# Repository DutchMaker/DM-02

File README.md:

# DM-02 8-Bit Computer

_Pronounced: "Dee-Em Zero Two"_

**An 8-bit computer built (almost) entirely out of TTL logic chips**  
This project started in September 2019 and is currently in progress.  
Please refer to the [documentation](./Documentation) for the project status.

**[Start by reading the introduction](./Documentation/)**

If you would like to see the computer in action, the best I can offer you now is the [DM-02 Emulator](https://dutchmaker.com/dm-02/emulator) while the electronic version is under development.

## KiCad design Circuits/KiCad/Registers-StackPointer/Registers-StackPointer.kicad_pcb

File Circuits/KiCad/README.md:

# KiCad projects

KiCad EDA is used for all circuit diagrams and PCB design.
Get it for free at: [http://kicad-pcb.org](http://kicad-pcb.org)

### KiCad setup:

- Add `./Libraries/*.lib` as global Symbol library to KiCad (Eeschema)
- Add the `./Libraries` folder as global Footprint library to KiCad (Pcbnew)

### Notes:

- The _FreeRouting_ application (`./Libraries/freeRouting.jar`) is used for initial PCB routing

### Credits:

- Arduino Mega Shield component: https://github.com/Alarm-Siren/arduino-kicad-library
- FreeRouting: https://freerouting.org/

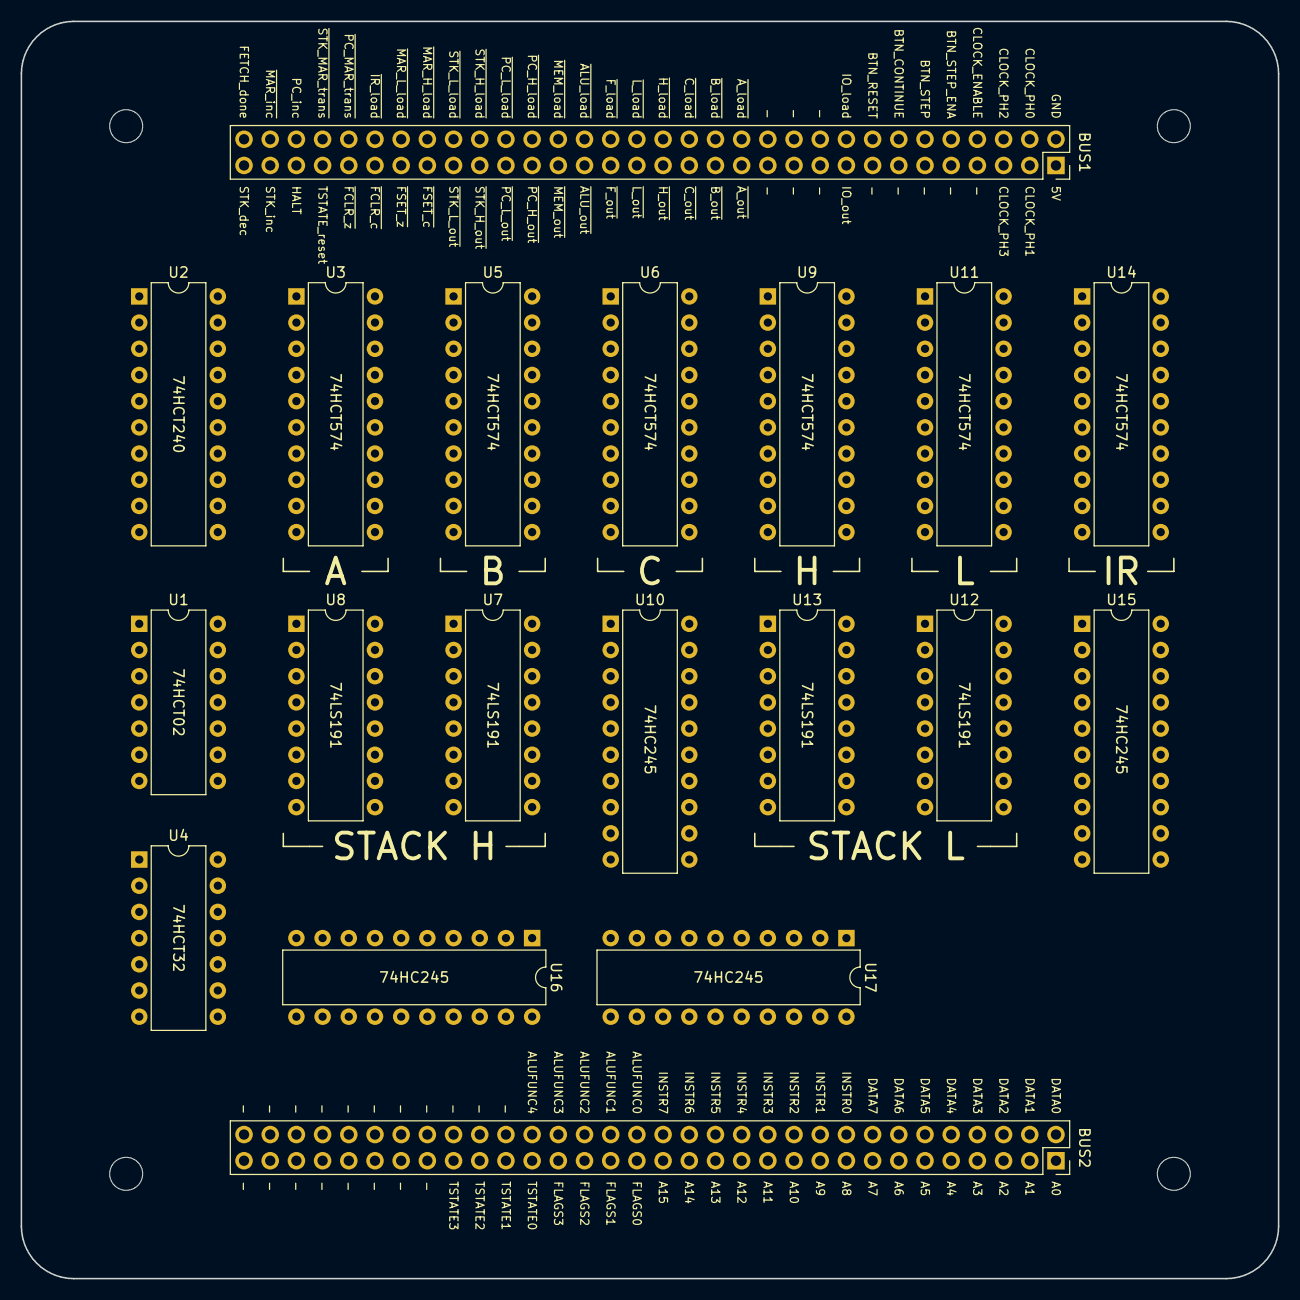
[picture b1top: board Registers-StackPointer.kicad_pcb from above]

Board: 2 copper layers, 121.9 x 121.9 mm, 23 parts (0 on the bottom side), 84 nets, no tracks yet.

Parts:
BUS1, BUS2: Conn_02x32_Odd_Even; PinSocket_2x32_P2.54mm_Vertical
H1, H2, H3, H4: MountingHole; MountingHole_3.2mm_M3
U1: 74HCT02; DIP-14_W7.62mm
U2: 74HCT240; DIP-20_W7.62mm
U3, U5, U6, U9, U11, U14: 74HCT574; DIP-20_W7.62mm
U4: 74HCT32; DIP-14_W7.62mm
U7, U8, U12, U13: 74LS191; DIP-16_W7.62mm
U10, U15, U16, U17: 74HC245; DIP-20_W7.62mm

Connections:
5V: BUS1.1, U2.20, U3.20, U5.20, U6.20, U7.16, U8.16, U9.20, U10.20, U11.20, U12.16, U13.16, U14.20, U15.20, U16.20, U17.20
A0: BUS2.1, U17.18
A1: BUS2.3, U17.17
A2: BUS2.5, U17.16
A3: BUS2.7, U17.15
A4: BUS2.9, U17.14
A5: BUS2.11, U17.13
A6: BUS2.13, U17.12
A7: BUS2.15, U17.11
A8: BUS2.17, U16.18
A9: BUS2.19, U16.17
A10: BUS2.21, U16.16
A11: BUS2.23, U16.15
A12: BUS2.25, U16.14
A13: BUS2.27, U16.13
A14: BUS2.29, U16.12
A15: BUS2.31, U16.11
A_clock: U2.18, U3.11
B_clock: U2.16, U5.11
CLOCK_PH3: BUS1.5, U1.11, U1.12, U4.2, U4.4, U12.14
C_clock: U2.14, U6.11
D0: U3.2, U3.19, U5.2, U5.19, U6.2, U6.19, U7.15, U9.2, U9.19, U10.18, U11.2, U11.19, U12.15, U14.2, U15.18
D1: U3.3, U3.18, U5.3, U5.18, U6.3, U6.18, U7.1, U9.3, U9.18, U10.17, U11.3, U11.18, U12.1, U14.3, U15.17
D2: U3.4, U3.17, U5.4, U5.17, U6.4, U6.17, U7.10, U9.4, U9.17, U10.16, U11.4, U11.17, U12.10, U14.4, U15.16
D3: U3.5, U3.16, U5.5, U5.16, U6.5, U6.16, U7.9, U9.5, U9.16, U10.15, U11.5, U11.16, U12.9, U14.5, U15.15
D4: U3.6, U3.15, U5.6, U5.15, U6.6, U6.15, U8.15, U9.6, U9.15, U10.14, U11.6, U11.15, U13.15, U14.6, U15.14
D5: U3.7, U3.14, U5.7, U5.14, U6.7, U6.14, U8.1, U9.7, U9.14, U10.13, U11.7, U11.14, U13.1, U14.7, U15.13
D6: U3.8, U3.13, U5.8, U5.13, U6.8, U6.13, U8.10, U9.8, U9.13, U10.12, U11.8, U11.13, U13.10, U14.8, U15.12
D7: U3.9, U3.12, U5.9, U5.12, U6.9, U6.12, U8.9, U9.9, U9.12, U10.11, U11.9, U11.12, U13.9, U14.9, U15.11
DOWN_~UP: U1.1, U1.5, U7.5, U8.5, U12.5, U13.5
GND: BUS1.2, U2.10, U3.10, U5.10, U6.10, U7.8, U8.8, U9.10, U10.1, U10.10, U11.10, U12.8, U13.8, U14.1, U14.10, U15.1, U15.10, U16.1, U16.10, U17.1, U17.10
HIGH0_Rc: U7.13, U8.14
H_clock: U2.12, U9.11
INSTR0: BUS2.18, U14.19
INSTR1: BUS2.20, U14.18
INSTR2: BUS2.22, U14.17
INSTR3: BUS2.24, U14.16
INSTR4: BUS2.26, U14.15
INSTR5: BUS2.28, U14.14
INSTR6: BUS2.30, U14.13
INSTR7: BUS2.32, U14.12
IR_clock: U2.5, U14.11
LOW0_Rc: U12.13, U13.14
LOW1_Rc: U7.14, U13.13
L_clock: U2.3, U11.11
unnamed: U1.3, U1.4
unnamed: U1.13, U2.1, U2.19
unnamed: U7.3, U10.2, U16.2
unnamed: U7.2, U10.3, U16.3
unnamed: U7.6, U10.4, U16.4
unnamed: U7.7, U10.5, U16.5
unnamed: U8.3, U10.6, U16.6
unnamed: U8.2, U10.7, U16.7
unnamed: U8.6, U10.8, U16.8
unnamed: U8.7, U10.9, U16.9
unnamed: U12.2, U15.3, U17.3
unnamed: U12.3, U15.2, U17.2
unnamed: U12.6, U15.4, U17.4
unnamed: U12.7, U15.5, U17.5
unnamed: U13.2, U15.7, U17.7
unnamed: U13.3, U15.6, U17.6
unnamed: U13.6, U15.8, U17.8
unnamed: U13.7, U15.9, U17.9
STK_dec: BUS1.63, U1.6, U1.9
STK_inc: BUS1.61, U1.2, U1.8
~A_load: BUS1.26, U2.2
~A_out: BUS1.25, U3.1
~B_load: BUS1.28, U2.4
~B_out: BUS1.27, U5.1
~CLK_EN: U1.10, U7.4, U8.4, U12.4, U13.4
~C_load: BUS1.30, U2.6
~C_out: BUS1.29, U6.1
~HIGH_PL: U4.3, U7.11, U8.11
~H_load: BUS1.32, U2.8
~H_out: BUS1.31, U9.1
~IR_load: BUS1.54, U2.15
~LOW_PL: U4.6, U12.11, U13.11
~L_load: BUS1.34, U2.17
~L_out: BUS1.33, U11.1
~STK_H_load: BUS1.46, U4.1
~STK_H_out: BUS1.45, U10.19
~STK_L_load: BUS1.48, U4.5
~STK_L_out: BUS1.47, U15.19
~STK_MAR_transfer: BUS1.58, U16.19, U17.19

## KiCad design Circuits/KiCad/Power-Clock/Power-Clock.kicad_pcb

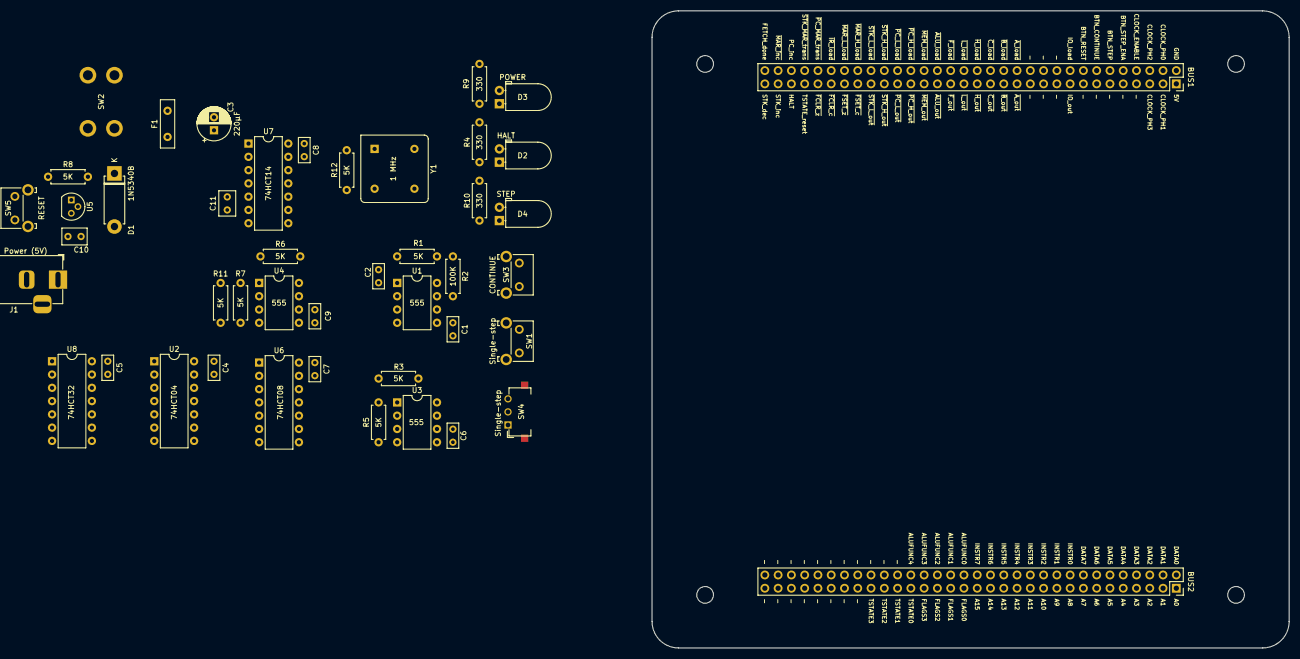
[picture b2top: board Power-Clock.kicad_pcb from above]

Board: 2 copper layers, 121.9 x 121.9 mm, 49 parts (0 on the bottom side), 34 nets, no tracks yet.

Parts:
BUS1, BUS2: Conn_02x32_Odd_Even; PinSocket_2x32_P2.54mm_Vertical
C1, C6, C9: 10nF; C_Rect_L4.6mm_W2.0mm_P2.50mm_MKS02_FKP02
C2, C4, C5, C7, C8: 100nF; C_Rect_L4.6mm_W2.0mm_P2.50mm_MKS02_FKP02
C3: 220µF; CP_Radial_D6.3mm_P2.50mm
C10: 100 nF; C_Rect_L4.6mm_W3.0mm_P2.50mm_MKS02_FKP02
C11: 1nF; C_Rect_L4.6mm_W3.0mm_P2.50mm_MKS02_FKP02
D1: 1N5340B; D_5W_P10.16mm_Horizontal
D2: HALT; LED_D5.0mm_Horizontal_O1.27mm_Z3.0mm
D3: POWER; LED_D5.0mm_Horizontal_O1.27mm_Z3.0mm
D4: STEP; LED_D5.0mm_Horizontal_O1.27mm_Z3.0mm
F1: Polyfuse; C_Disc_D9.0mm_W2.5mm_P5.00mm
H1, H2, H3, H4: MountingHole; MountingHole_3.2mm_M3
J1: Power (5V); BarrelJack_Horizontal
R1, R3, R5, R6, R7, R8, R11, R12: 5K; R_Axial_DIN0207_L6.3mm_D2.5mm_P7.62mm_Horizontal
R2: 100K; R_Axial_DIN0207_L6.3mm_D2.5mm_P7.62mm_Horizontal
R4, R9, R10: 330; R_Axial_DIN0207_L6.3mm_D2.5mm_P7.62mm_Horizontal
SW1: Single-step; SW_Tactile_SKHH_Angled
SW2: Power; Switch_DPST_Angled
SW3: CONTINUE; SW_Tactile_SKHH_Angled
SW4: Single-step; Slide-switch
SW5: RESET; SW_Tactile_SKHH_Angled
U1, U3, U4: 555; DIP-8_W7.62mm
U2: 74HCT04; DIP-14_W7.62mm
U5: MCP100-450D; TO-92
U6: 74HCT08; DIP-14_W7.62mm
U7: 74HCT14; DIP-14_W7.62mm
U8: 74HCT32; DIP-14_W7.62mm
Y1: 1 MHz; Oscillator_DIP-8_v2

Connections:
CLK_OSC: U6.5, Y1.3
CLK_STEP: U1.3, U6.1
CLOCK1: U6.11, U7.1, U7.3
CLOCK2: U7.6, U7.9
CLOCK_ENABLE: R12.2, U6.12
COMPUTER_5V: C3.1, C4.1, C5.1, C7.1, C8.1, C10.2, D1.1, F1.1, R1.2, R2.1, R3.2, R5.2, R6.2, R7.2, R8.2, R12.1, SW3.1, U1.4, U1.8, U2.14, U3.8, U4.8, U5.2, U6.14, U7.14, U8.14, Y1.1
COMPUTER_GND: C1.2, C2.2, C3.2, C4.2, C5.2, C6.2, C7.2, C8.2, C9.2, C10.1, C11.1, D1.2, R4.2, R9.1, R10.2, R11.1, SW1.1, SW2.2, SW4.2, SW5.1, U1.1, U2.7, U3.1, U3.6, U4.1, U4.6, U5.3, U6.7, U7.7, U8.7, Y1.2
CONTINUE: SW3.2, U2.1
HALT: D2.2, R7.1, U2.5, U4.4
unnamed: C1.1, U1.5
unnamed: C2.1, R2.2, U1.6, U1.7
unnamed: C6.1, U3.5
unnamed: C9.1, U4.5
unnamed: C11.2, U7.4, U7.5
unnamed: D2.1, R4.1
unnamed: D3.1, R9.2
unnamed: D4.1, R10.1
unnamed: F1.2, SW2.4
unnamed: J1.1, SW2.3
unnamed: J1.2, SW2.1
unnamed: R1.1, SW1.2, U1.2
unnamed: R3.1, SW4.1, U3.2
unnamed: R5.1, SW4.3, U3.4
unnamed: R6.1, U2.2, U4.2
unnamed: R11.2, U4.3, U8.2
unnamed: U2.4, U6.4
unnamed: U2.6, U8.1
unnamed: U6.3, U8.4
unnamed: U6.6, U8.5
unnamed: U6.9, U8.6
unnamed: U6.10, U8.3
unnamed: U6.8, U6.13
STEP_EN: D4.2, U2.3, U3.3, U6.2
~RESET: D3.2, R8.1, SW5.2, U5.1

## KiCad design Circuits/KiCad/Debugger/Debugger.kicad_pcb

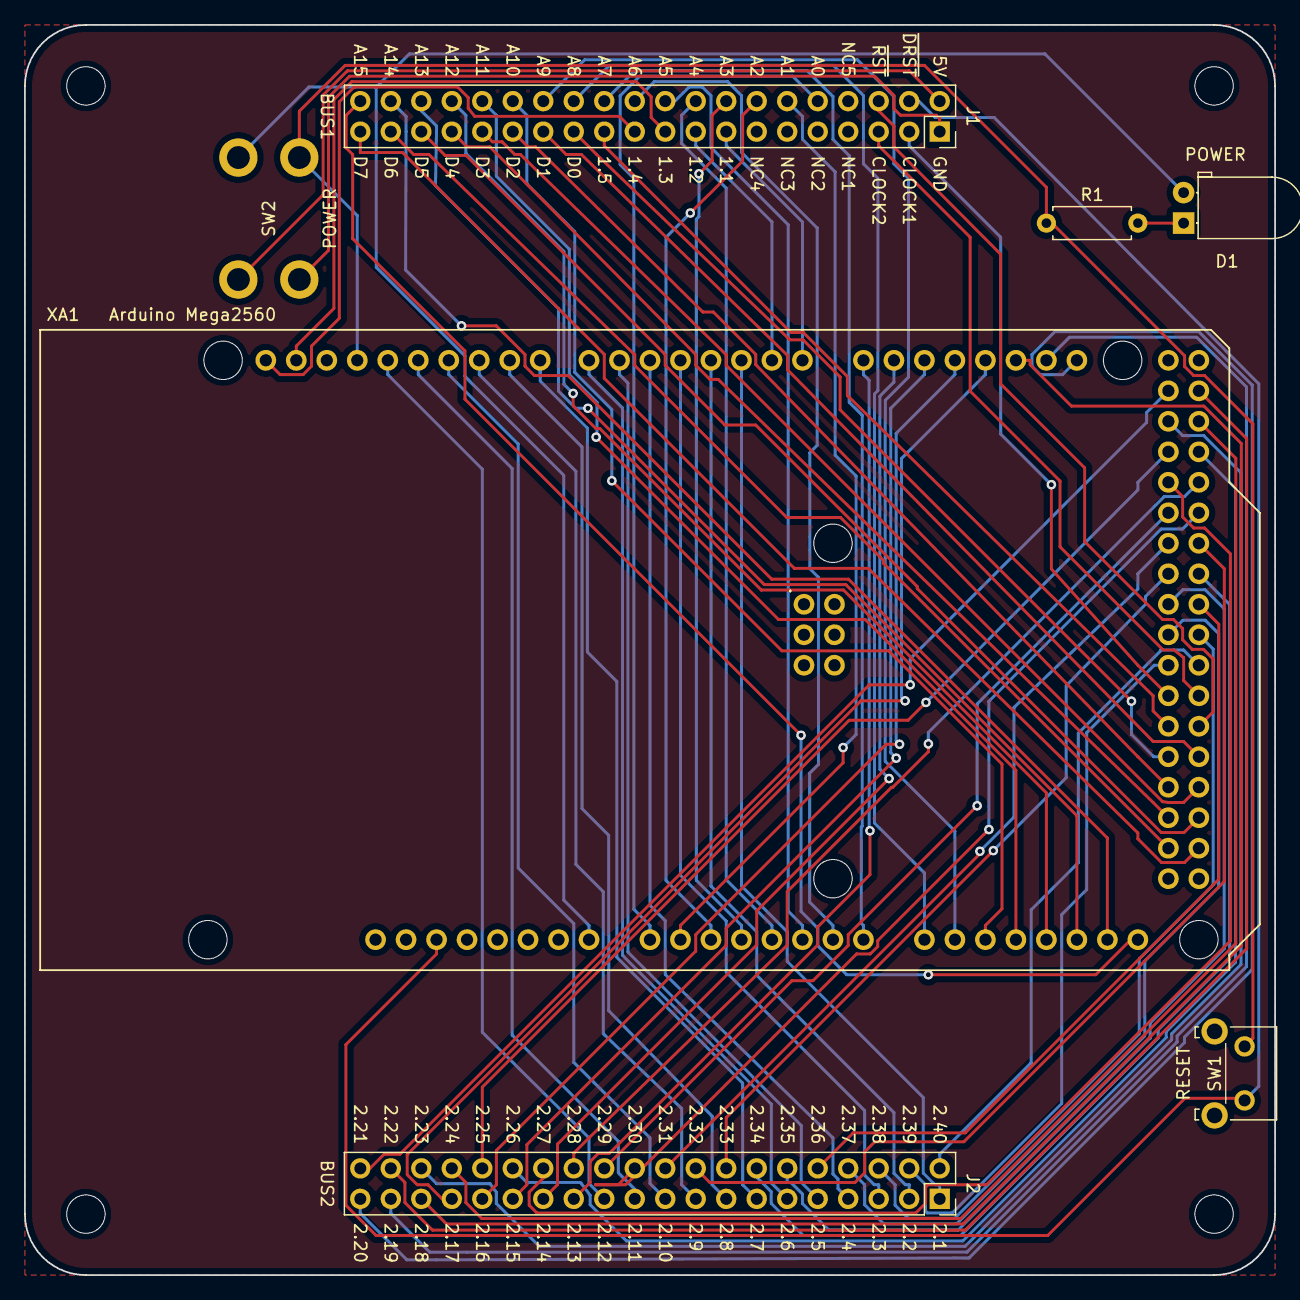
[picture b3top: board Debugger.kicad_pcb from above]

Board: 2 copper layers, 104.1 x 104.1 mm, 11 parts (0 on the bottom side), 78 nets.

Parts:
D1: POWER; LED_D5.0mm_Horizontal_O1.27mm_Z3.0mm
H1, H2, H3, H4: MountingHole; MountingHole_3.2mm_M3
J1: BUS1; PinSocket_2x20_P2.54mm_Vertical
J2: BUS2; PinSocket_2x20_P2.54mm_Vertical
R1: 330; R_Axial_DIN0207_L6.3mm_D2.5mm_P7.62mm_Horizontal
SW1: RESET; SW_Tactile_SKHH_Angled
SW2: POWER; Switch_DPST_Angled
XA1: Arduino Mega2560; Arduino_Mega2560_Shield

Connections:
A0: J1.10, XA1.A0
A1: J1.12, XA1.A1
A2: J1.14, XA1.A2
A3: J1.16, XA1.A3
A4: J1.18, XA1.A4
A5: J1.20, XA1.A5
A6: J1.22, XA1.A6
A7: J1.24, XA1.A7
A8: J1.26, XA1.A8
A9: J1.28, XA1.A9
A10: J1.30, XA1.A10
A11: J1.32, XA1.A11
A12: J1.34, XA1.A12
A13: J1.36, XA1.A13
A14: J1.38, XA1.A14
A15: J1.40, XA1.A15
ARDUINO_5V: D1.2, SW2.2, XA1.VIN
ARDUINO_GND: R1.1, SW1.1, SW2.4, XA1.GND1
BUS1_1: J1.15, XA1.D0
BUS1_2: J1.17, XA1.D1
BUS1_3: J1.19, XA1.SDA
BUS1_4: J1.21, XA1.SCL
BUS1_5: J1.23, XA1.D44
BUS2_1: J2.1, XA1.D2
BUS2_2: J2.3, XA1.D3
BUS2_3: J2.5, XA1.D4
BUS2_4: J2.7, XA1.D5
BUS2_5: J2.9, XA1.D6
BUS2_6: J2.11, XA1.D7
BUS2_7: J2.13, XA1.D8
BUS2_8: J2.15, XA1.D9
BUS2_9: J2.17, XA1.D10
BUS2_10: J2.19, XA1.D11
BUS2_11: J2.21, XA1.D12
BUS2_12: J2.23, XA1.D13
BUS2_13: J2.25, XA1.D14
BUS2_14: J2.27, XA1.D15
BUS2_15: J2.29, XA1.D16
BUS2_16: J2.31, XA1.D17
BUS2_17: J2.33, XA1.D18
BUS2_18: J2.35, XA1.D19
BUS2_19: J2.37, XA1.D20
BUS2_20: J2.39, XA1.D21
BUS2_21: J2.40, XA1.D22
BUS2_22: J2.38, XA1.D23
BUS2_23: J2.36, XA1.D24
BUS2_24: J2.34, XA1.D25
BUS2_25: J2.32, XA1.D26
BUS2_26: J2.30, XA1.D27
BUS2_27: J2.28, XA1.D28
BUS2_28: J2.26, XA1.D29
BUS2_29: J2.24, XA1.D30
BUS2_30: J2.22, XA1.D31
BUS2_31: J2.20, XA1.D32
BUS2_32: J2.18, XA1.D33
BUS2_33: J2.16, XA1.D34
BUS2_34: J2.14, XA1.D35
BUS2_35: J2.12, XA1.D36
BUS2_36: J2.10, XA1.D37
BUS2_37: J2.8, XA1.D38
BUS2_38: J2.6, XA1.D39
BUS2_39: J2.4, XA1.D40
BUS2_40: J2.2, XA1.D41
CLOCK1: J1.3, XA1.D42
CLOCK2: J1.5, XA1.D43
COMPUTER_5V: J1.2, SW2.1
COMPUTER_GND: J1.1, SW2.3
D0: J1.25, XA1.D46
D1: J1.27, XA1.D47
D2: J1.29, XA1.D48
D3: J1.31, XA1.D49
D4: J1.33, XA1.D50
D5: J1.35, XA1.D51
D6: J1.37, XA1.D52
D7: J1.39, XA1.D53
unnamed: D1.1, R1.2
~DEBUG_RESET: J1.4, SW1.2, XA1.RST1
~RESET: J1.6, XA1.D45

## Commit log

2019-09-26 Preparing microcode language
2019-09-27 Started work on simulation
2019-09-28 Decided to go with Logisim for simulation
2019-09-28 Working on ALU implementation for Logisim
2019-09-29 Finished Program Counter in Logisim
2019-09-29 Added ALU ROM data generator from @DoctorWkt his CSCvon8 project
2019-09-29 Added Stack Pointer to Logisim design
2019-09-29 Work in progress on Memory Access Register in Logisim
2019-09-30 Improved ALU <> Accumulator connection
2019-09-30 Added Memory module to Logisim design
2019-09-30 Work in progress on Flags Register
2019-10-01 Logisim design, excluding Controller module, is pretty much done
2019-10-01 Added ALU functions to microcode source format
2019-10-02 Microcode Compiler work in progress..
2019-10-02 Microcode compiler is generating ROM and Logisim image (still needs testing)
2019-10-03 Working on decoding circuit
2019-10-04 Work in progress on controller logic
2019-10-05 First instruction being executed in Logisim
2019-10-09 Fixed A register override issue
2019-10-11 Still struggling with the control unit in Logisim...
2019-10-16 Control unit now working thanks to synchronous reset counter
2020-02-22 Updated gitignore
2020-02-22 Started work on an emulator
2020-02-24 Work in progress on emulator
2020-02-28 Doc update
2020-02-29 Testing new fetch cycle circuit
2020-03-01 Fixing fetch cycle
2020-03-02 Fixed fetch cycle in Logisim
2020-04-15 Updated PCB for Bottom and Debugger (sent to manufacturer)
2020-04-16 Working out clock module
2020-04-18 Updated clock circuit
2020-04-18 Tested clock circuit
2020-04-18 Footprint fix switch
2020-04-21 Routed power & clock PCB
2020-04-24 Attempt to improve Logisim circuit
2020-04-26 Improving logisim circuit
2020-04-27 Implementing more microcode
2020-04-27 Implemented MAR_inc in Logisim circuit
2020-04-27 All MOV instructions microcode implemented
2020-04-27 Stack instructions implemented
2020-04-28 Fixed program counter bug and implemented flags pop
2020-04-28 Fixed microcode compiler bug
2020-04-28 Added more microcode
2020-04-28 All microcode implemented!
2020-04-28 Re-assigned opcodes
2020-04-28 Hello world
2020-04-28 Doing some restructuring of the Logisim circuit
2020-04-28 Restructuring Logisim circuit
2020-04-28 Finished restructuring
2020-04-28 Work in progress on assembler
2020-04-29 Finished the assembler and got the example program running in Logisim!
2020-04-30 Programs can now run from RAM
2020-04-30 Fixed assembler bug to resolved instructions incorrectly
2020-04-30 Basic video display working
2020-04-30 Updated example bitmap data
2020-05-01 Added breakpoint handler to Logisim circuit
2020-05-01 Fixed issue with offset. Added reset logic to circuit
2020-05-01 Assembler now displays pointer variables in output
2020-05-01 Documentation updates
2020-05-01 Documentation
2020-05-01 More docs
2020-05-02 Improved bitmap program speed
2020-05-04 Ditched work on the emulator in dotnetcore and started building one in javascript with web interface
2020-05-11 Emulator can now load programs from disk
2020-05-11 All instructions implemented in emulator
2020-05-12 Emulator fully functional
2020-05-12 Minor emulator fixes and added loading from server
2020-05-12 Bugfix
2020-05-19 Figuring out bus connections
2020-06-29 Updated bus connections and bottom plate design
2020-07-13 Register/stack schematic & PCB
2020-07-30 Did a bit of work on circuit design
2020-08-13 Working on memory circuit design
2020-08-14 Memory circuit
